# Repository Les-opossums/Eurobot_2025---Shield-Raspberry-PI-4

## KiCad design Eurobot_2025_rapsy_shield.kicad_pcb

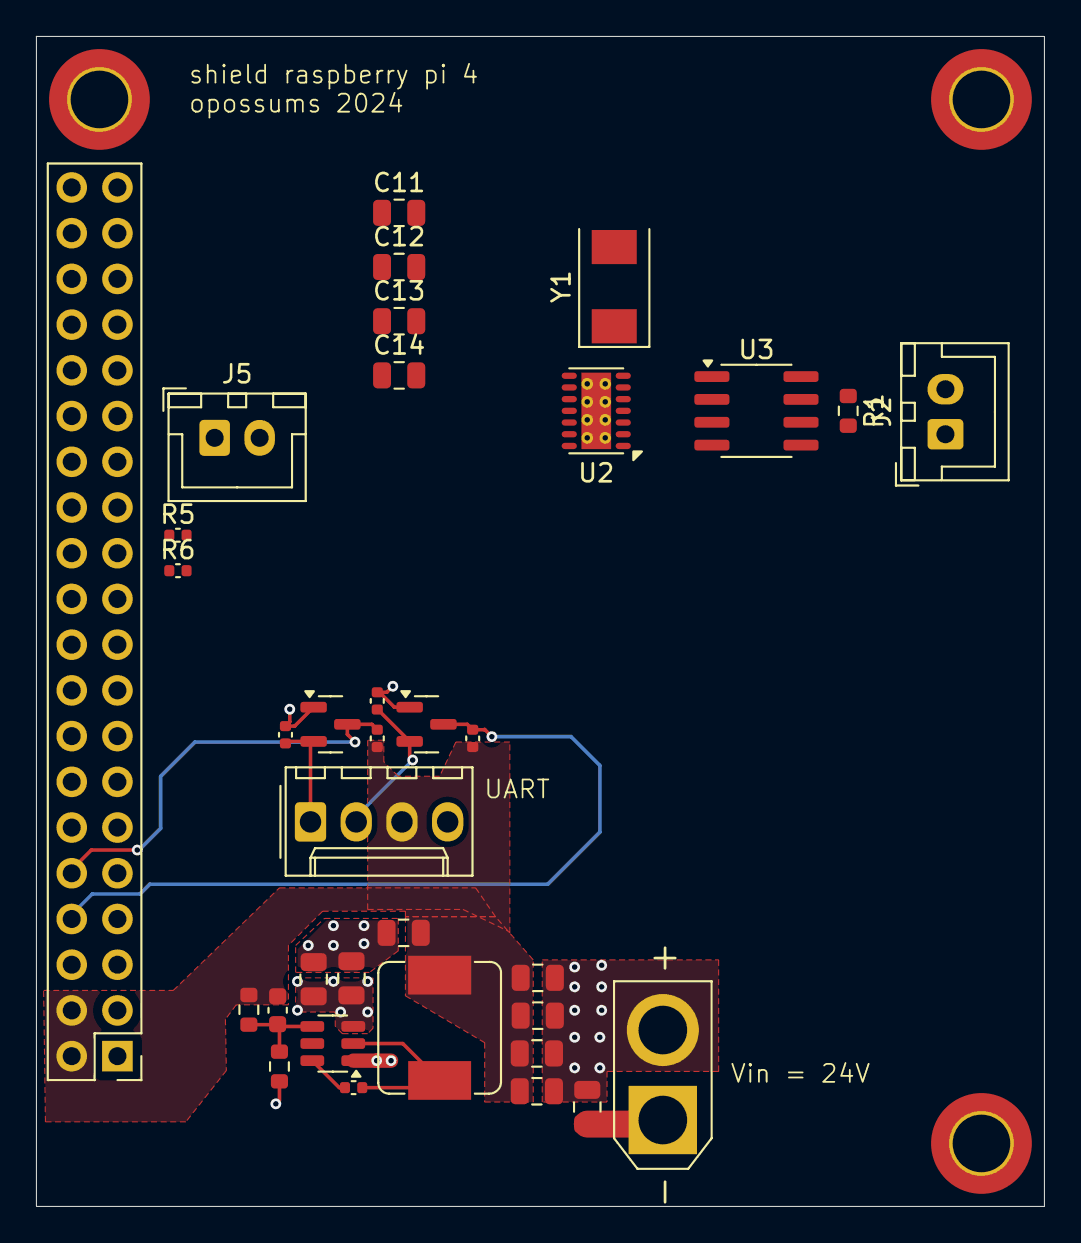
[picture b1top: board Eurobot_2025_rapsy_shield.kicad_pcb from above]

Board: 2 copper layers, 56.0 x 65.0 mm, 38 parts (0 on the bottom side), 23 nets.

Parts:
C1, C2: 10µF 50V; C_0805_2012Metric
C3: 100nF 50V; C_0805_2012Metric
C4: 100nF 50V; C_0402_1005Metric
C5: 150pF 50V; C_0603_1608Metric
C6, C7, C8, C9, C10: 22µF 25V; C_0805_2012Metric
C11: 0.1uF 10V; C_0805_2012Metric
C12, C13: 22pF; C_0805_2012Metric
C14: 0.1uF; C_0805_2012Metric
H1, H3, H4: MountingHole_Pad; MountingHole_3.2mm_M3_DIN965_Pad_TopBottom
J1: Raspberry_Pi_2_3; PinHeader_2x20_P2.54mm_Vertical
J2: CAN; JST_XH_B2B-XH-A_1x02_P2.50mm_Vertical
J4: Conn_01x02; AMASS_XT30U-F_1x02_P5.0mm_Vertical
J5: AU; JST_XH_B2B-XH-A_1x02_P2.50mm_Vertical
J6: Conn_01x04; Molex_KK-254_AE-6410-04A_1x04_P2.54mm_Vertical
L1: PSPMAQ0605H-150M-ANP; Prod_Tech_7.1x6.6mm
Q1, Q2: 2N7002; SOT-23
R1: 120R; R_0603_1608Metric
R3: 100k; R_0603_1608Metric
R4: 13.3k; R_0603_1608Metric
R5: 1k; C_0402_1005Metric
R6: 100R; C_0402_1005Metric
R7, R8, R9, R10: 10k; C_0402_1005Metric
U1: TPS54302; SOT-23-6
U2: MCP2518FD-xQBB; DFN-14-1EP_3x4.5mm_P0.65mm_EP1.65x4.25mm_ThermalVias
U3: ATA6563; SOIC-8_3.9x4.9mm_P1.27mm
Y1: 20MHz; Crystal_SMD_0603-2Pin_6.0x3.5mm

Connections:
3.3V: C11.2, C14.2, J1.1 (3V3), J1.17 (3V3), Q1.1 (G), Q2.1 (G), R5.1, R7.1, R8.1, U2.14 (VDD), U3.5 (VIO)
5V: C5.1, C6.1, C7.1, C8.1, C9.1, C10.1, J1.2 (5V), J1.4 (5V), J6.3, L1.2, R3.1, R9.1, R10.1
/Vin: C1.1, C2.1, C3.1, J4.1, U1.3 (VIN)
AU: J1.18 (GPIO24), R5.2, R6.2
CE0: J1.24 (~CE0/GPIO8), U2.13 (~CS)
GND: C1.2, C2.2, C3.2, C6.2, C7.2, C8.2, C9.2, C10.2, C11.1, C12.1, C13.1, C14.1, H1.1, H3.1, H4.1, J1.6 (GND), J1.9 (GND), J1.14 (GND), J1.20 (GND), J1.25 (GND), J1.30 (GND), J1.34 (GND), J1.39 (GND), J4.2, J5.2, J6.4, R4.2, U1.1 (GND), U2.7 (VSS), U2.15 (VSS), U3.2 (GND), U3.3 (VCC), U3.8 (STBY)
MISO: J1.21 (MISO0/GPIO9), U2.12 (SDO)
MOSI: J1.19 (MOSI0/GPIO10), U2.11 (SDI)
unnamed: J2.1, R1.2, U3.6 (CANL)
unnamed: J2.2, R1.1, U3.7 (CANH)
unnamed: J5.1, R6.1
unnamed: J6.1, Q1.2 (S), R7.2
unnamed: J6.2, Q2.2 (S), R8.2
unnamed: C4.1, U1.6 (BOOT)
unnamed: C5.2, R3.2, R4.1, U1.4 (FB)
unnamed: C4.2, L1.1, U1.2 (SW)
unnamed: C13.2, U2.6 (OSC1), Y1.1
unnamed: C12.2, U2.5 (OSC2), Y1.2
unnamed: U2.2 (RXCAN), U3.4 (RXD)
unnamed: U2.1 (TXCAN), U3.1 (TXD)
RX: J1.10 (GPIO15/RXD), Q1.3 (D), R9.2
SCLK: J1.23 (SCLK0/GPIO11), U2.10 (SCK)
TX: J1.8 (GPIO14/TXD), Q2.3 (D), R10.2

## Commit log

2024-08-18 v1 ok
2024-09-04 schematic for can
